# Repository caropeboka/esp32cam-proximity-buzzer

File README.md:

# esp32cam-proximity-buzzer

This is an ESP32CAM Project with proximity sensor, buzzer, ftdi, and blynk app for detecting illegal parking in the neighborhood. For the schematic and board we use Eagle and for the 3D design we use Fusion 360 with acrylic material. We have made this project for Product Engineering Workshop Final Project Assignment.

Schematic:

Board:

Blynk:

3D Design:
https://grabcad.com/library/esp32cam-proximity-buzzer-1

Implementation:

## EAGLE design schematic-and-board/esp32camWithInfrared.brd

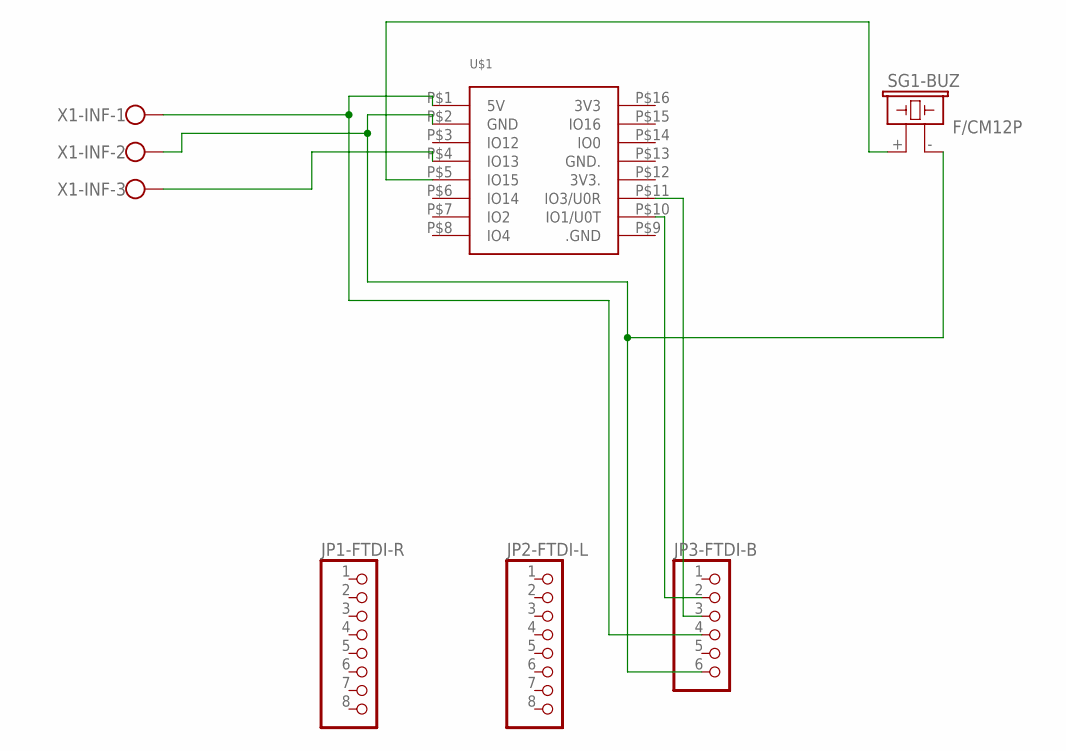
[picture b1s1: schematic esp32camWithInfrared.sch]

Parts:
JP1-FTDI-R, JP2-FTDI-L: PINHD-1X8; 1X08
JP3-FTDI-B: PINHD-1X6; 1X06
SG1-BUZ: F/CM12P
U$1: ESP32-CAM
X1-INF: W237-103

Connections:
unnamed: JP3-FTDI-B.6, SG1-BUZ.- (2), U$1.P$2 (GND), X1-INF.2
unnamed: JP3-FTDI-B.2, U$1.P$10 (IO1/U0T)
unnamed: JP3-FTDI-B.3, U$1.P$11 (IO3/U0R)
unnamed: JP3-FTDI-B.4, U$1.P$1 (5V), X1-INF.1
unnamed: SG1-BUZ.+ (1), U$1.P$5 (IO15)
unnamed: U$1.P$4 (IO13), X1-INF.3

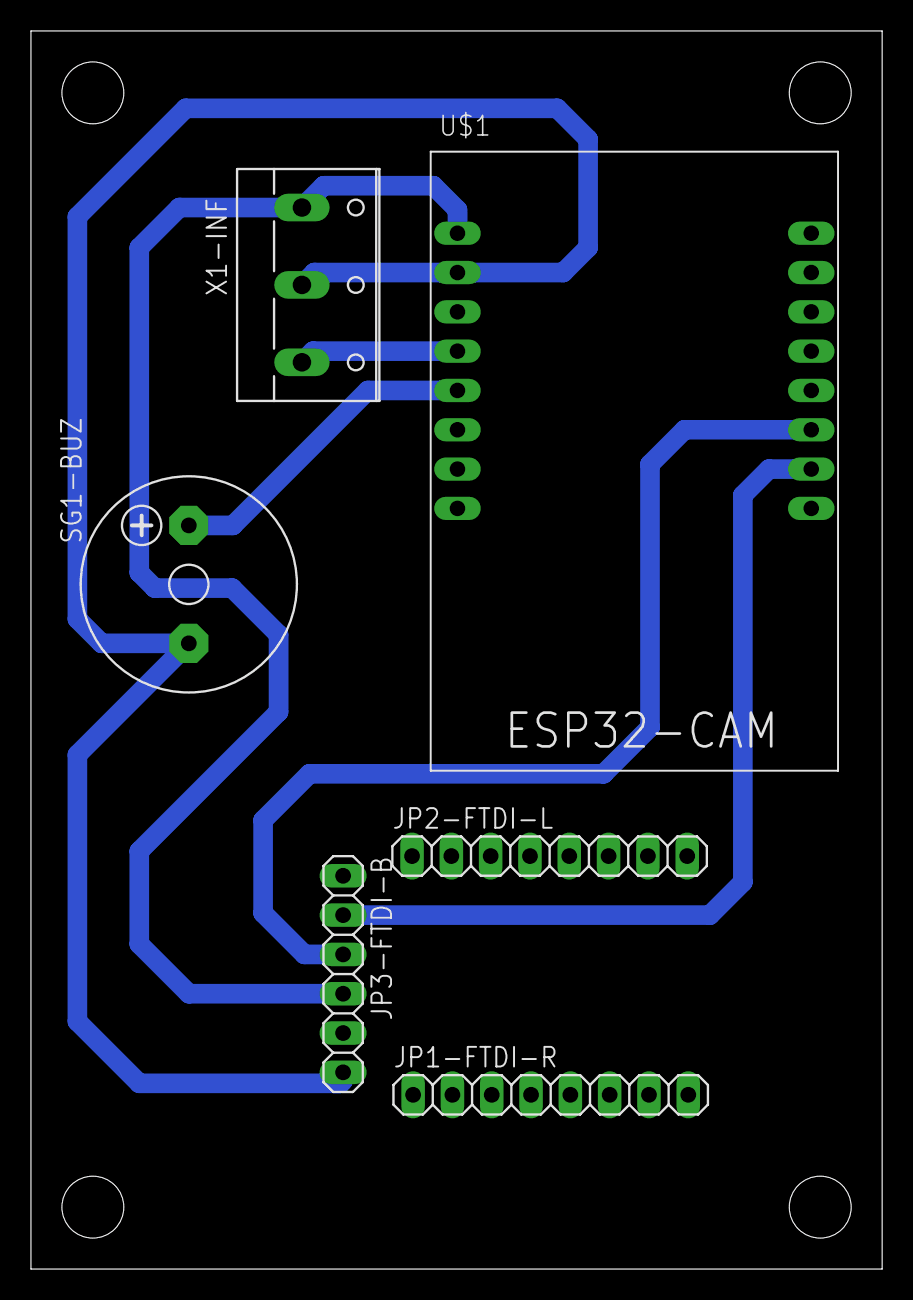
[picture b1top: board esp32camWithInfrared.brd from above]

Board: 2 copper layers, 55.0 x 80.0 mm, 6 parts (0 on the bottom side), 6 nets.
